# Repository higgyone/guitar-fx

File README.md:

# guitar-fx
Creating guitar pedal effects using an FPGA and VHDL. This is a learning experience to understand how to write digital signal processing effects for an FPGA

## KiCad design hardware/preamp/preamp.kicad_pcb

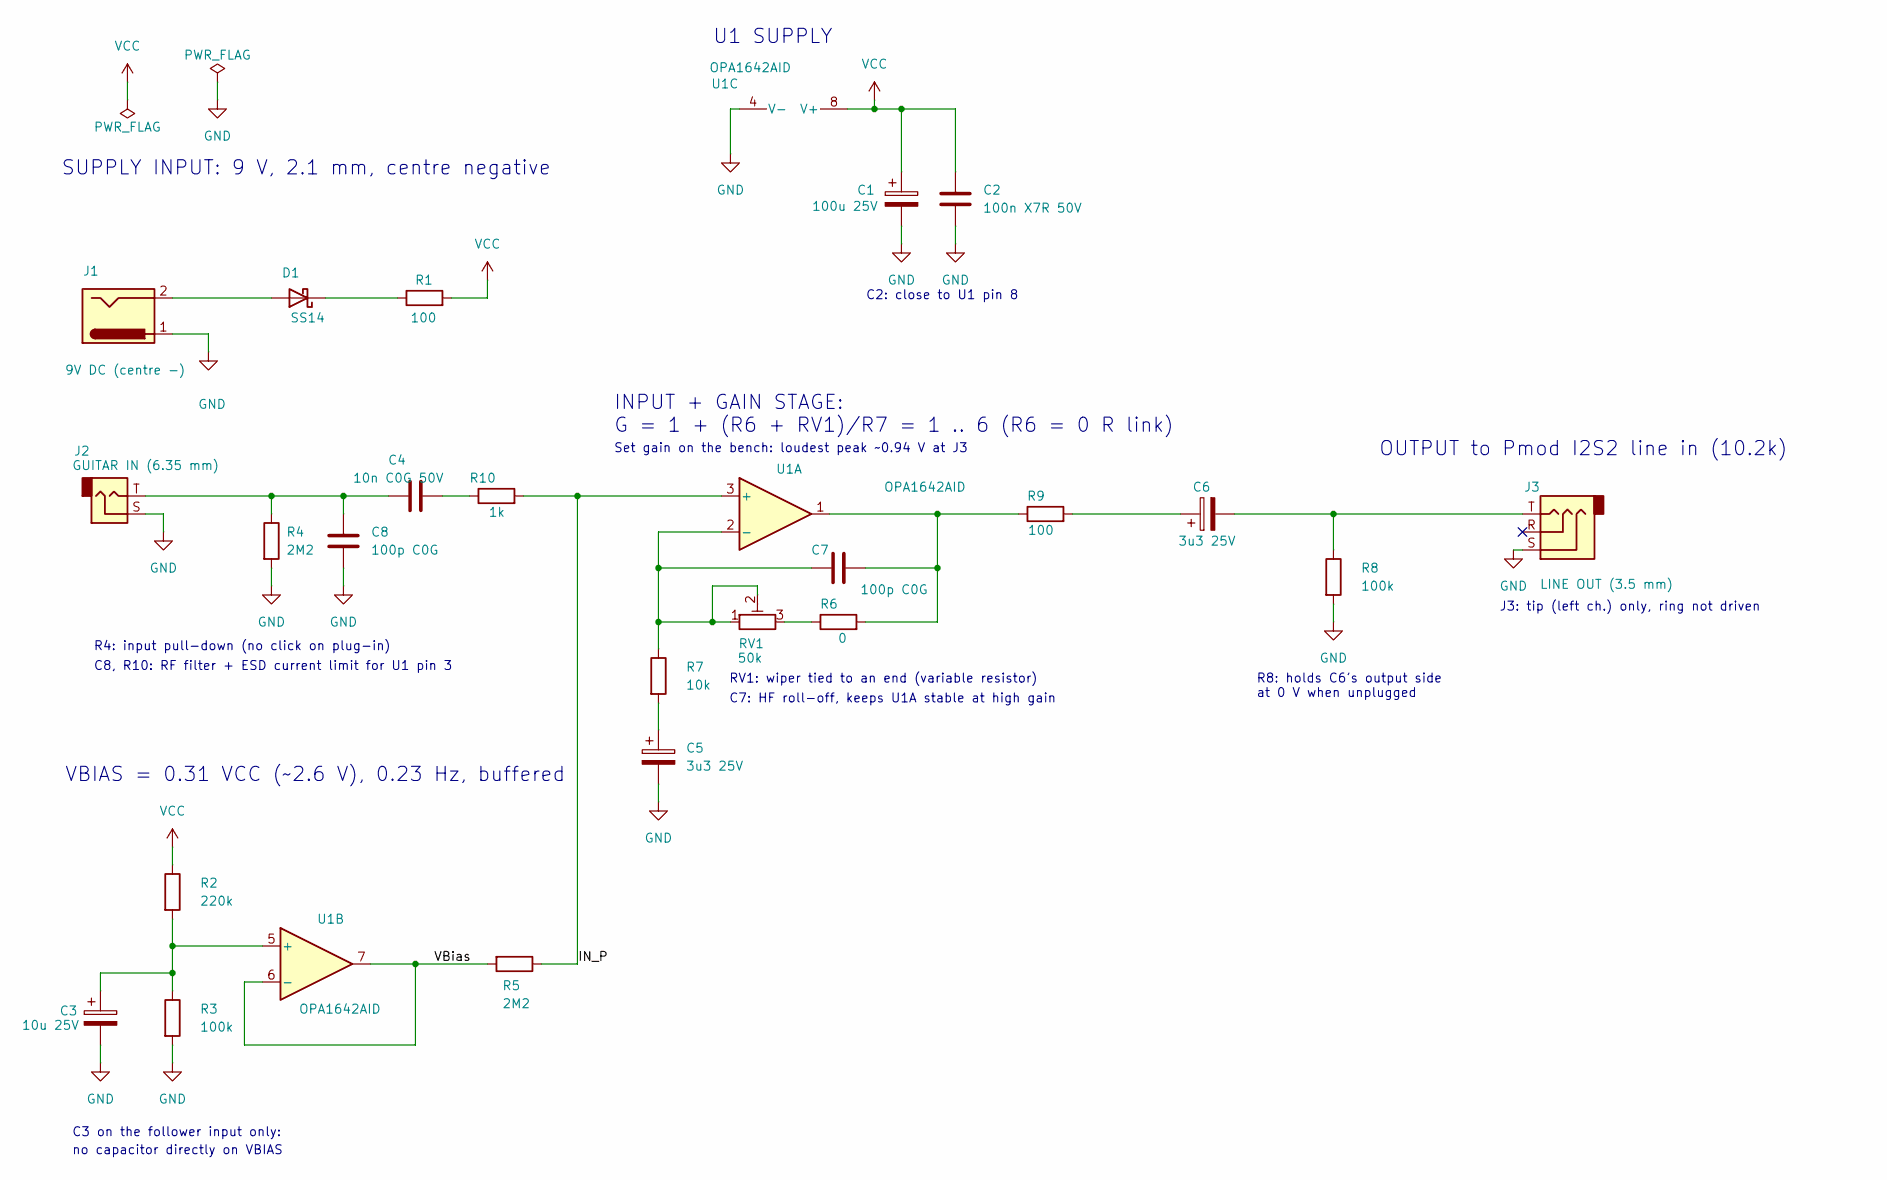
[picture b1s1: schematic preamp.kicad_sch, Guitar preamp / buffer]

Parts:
C1: 100u 25V; CP_Elec_6.3x7.7
C2: 100n X7R 50V; C_0603_1608Metric_Pad1.08x0.95mm_HandSolder
C3: 10u 25V; CP_Elec_4x5.4
C4: 10n C0G 50V; C_0402_1005Metric_Pad0.74x0.62mm_HandSolder
C5, C6: 3u3 25V; CP_Elec_4x5.4
C7: 100p C0G; C_0402_1005Metric_Pad0.74x0.62mm_HandSolder
C8: 100p C0G; C_0603_1608Metric_Pad1.08x0.95mm_HandSolder
D1: SS14; D_SMA_Handsoldering
J1: 9V DC (centre -); BarrelJack_CUI_PJ-102AH_Horizontal
J2: GUITAR IN (6.35 mm); Jack_6.35mm_Neutrik_NMJ4HCD2_Horizontal
J3: LINE OUT (3.5 mm); Jack_3.5mm_CUI_SJ1-3523N_Horizontal
R1, R9: 100; R_0603_1608Metric_Pad0.98x0.95mm_HandSolder
R2: 220k; R_0603_1608Metric_Pad0.98x0.95mm_HandSolder
R3, R8: 100k; R_0603_1608Metric_Pad0.98x0.95mm_HandSolder
R4, R5: 2M2; R_0603_1608Metric_Pad0.98x0.95mm_HandSolder
R6: 0; R_0603_1608Metric_Pad0.98x0.95mm_HandSolder
R7: 10k; R_0603_1608Metric_Pad0.98x0.95mm_HandSolder
R10: 1k; R_0603_1608Metric_Pad0.98x0.95mm_HandSolder
RV1: 50k; Potentiometer_Bourns_3296W_Vertical
U1: OPA1642AID; SOIC-8_3.9x4.9mm_P1.27mm

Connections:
/IN_P: R5.1, R10.2, U1.3 (+)
/VBias: R5.2, U1.6 (-), U1.7
GND: C1.2, C2.2, C3.2, C5.2, C8.2, J1.1, J2.S, J3.S, R3.2, R4.2, R8.2, U1.4 (V-)
unnamed: C4.1, C8.1, J2.T, R4.1
unnamed: C4.2, R10.1
unnamed: C5.1, R7.2
unnamed: C6.1, R9.2
unnamed: C6.2, J3.T, R8.1
unnamed: C7.2, R6.2, R9.1, U1.1
unnamed: D1.2 (A), J1.2
unnamed: D1.1 (K), R1.1
unnamed: R6.1, RV1.3
unnamed: C7.1, R7.1, RV1.1, RV1.2, U1.2 (-)
unnamed: C3.1, R2.2, R3.1, U1.5 (+)
VCC: C1.1, C2.1, R1.2, R2.1, U1.8 (V+)

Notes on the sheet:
C3 on the follower input only:
R8: holds C6's output side at 0 V when unplugged
SUPPLY INPUT: 9 V, 2.1 mm, centre negative
no capacitor directly on VBIAS
J3: tip (left ch.) only, ring not driven
Set gain on the bench: loudest peak ~0.94 V at J3
INPUT + GAIN STAGE: G = 1 + (R6 + RV1)/R7 = 1 .. 6 (R6 = 0 R link)
R4: input pull-down (no click on plug-in)
C2: close to U1 pin 8
RV1: wiper tied to an end (variable resistor)
OUTPUT to Pmod I2S2 line in (10.2k)
VBIAS = 0.31 VCC (~2.6 V), 0.23 Hz, buffered
U1 SUPPLY
C8, R10: RF filter + ESD current limit for U1 pin 3
C7: HF roll-off, keeps U1A stable at high gain

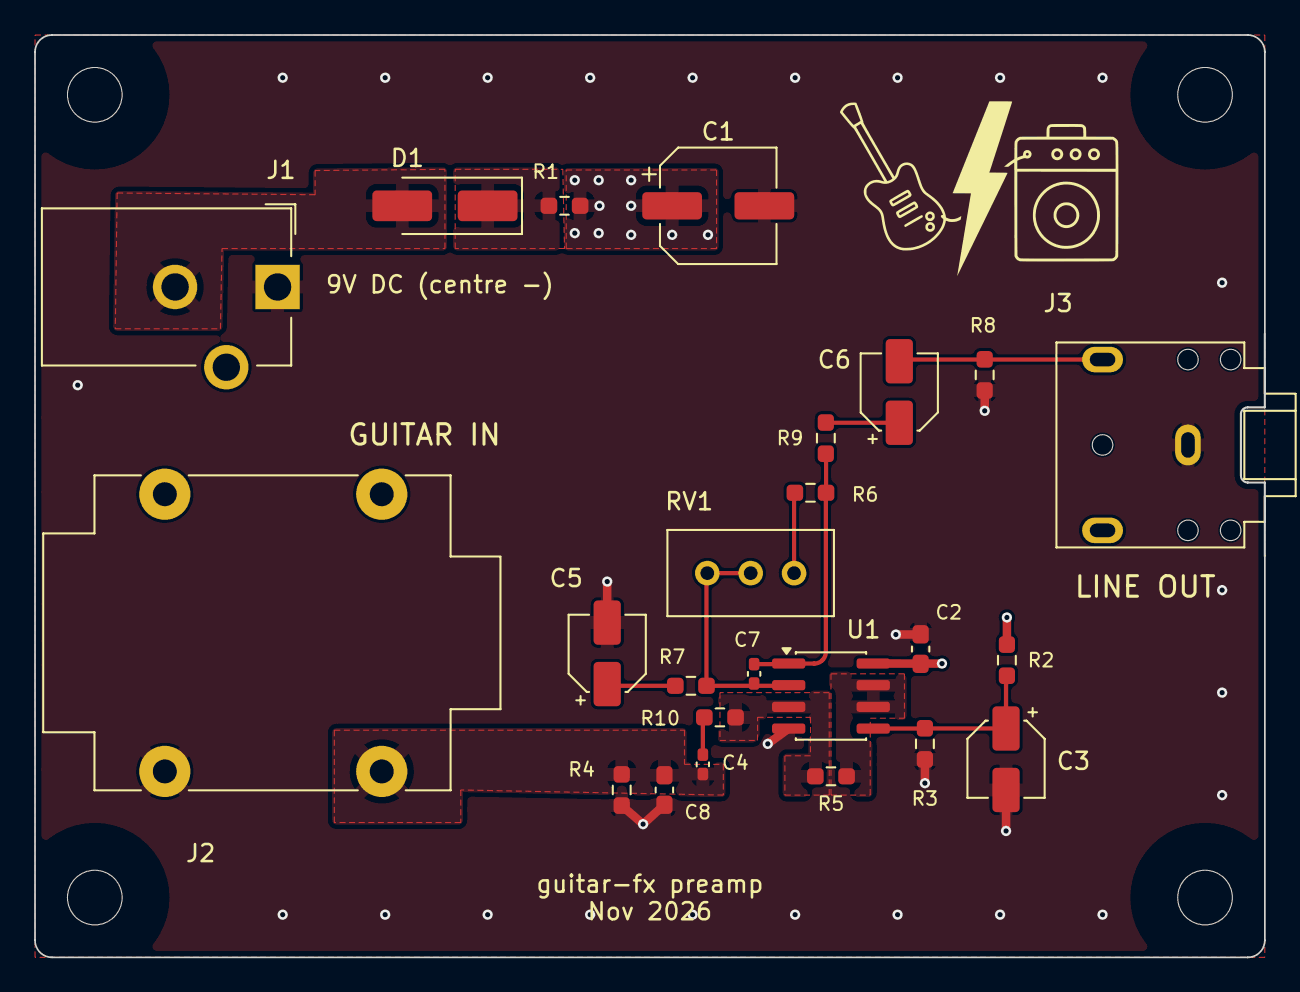
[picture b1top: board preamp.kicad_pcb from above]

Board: 4 copper layers, 72.0 x 54.0 mm, 28 parts (0 on the bottom side), 15 nets.

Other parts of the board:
H1, H2, H3, H4: M3; MountingHole_3.2mm_M3

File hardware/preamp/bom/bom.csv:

Ref,Qty per board,Value,Footprint,Manufacturer,MPN,Notes
U1,1,OPA1642AID,SOIC-8,Texas Instruments,OPA1642AID,DigiKey only (not at Mouser or RS)
J1,1,DC jack 2.0 mm pin (centre -),BarrelJack_CUI_PJ-102AH_Horizontal,Same Sky,PJ-102AH,
J2,1,6.35 mm mono switched,Jack_6.35mm_Neutrik_NMJ4HCD2_Horizontal,Neutrik,NMJ4HCD2,
J3,1,3.5 mm stereo,Jack_3.5mm_CUI_SJ1-3523N_Horizontal,Same Sky,SJ1-3523N,
D1,1,SS14 40 V 1 A Schottky,D_SMA,Vishay,SS14-E3/61T,Any SMA SS14 (onsemi SS14 at RS)
RV1,1,50k multi-turn trimmer,Bourns 3296W,Bourns,3296W-1-503LF,
C1,1,100u 25V,CP_Elec_6.3x7.7,Nichicon,UCD1E101MCL1GS,Or Panasonic EEE-FK1E101P (RS has it; Mouser/DigiKey out of stock)
C2,1,100n X7R 50V,0603,Yageo,CC0603KRX7R9BB104,
C3,1,10u 25V,CP_Elec_4x5.4,Panasonic,EEE-FK1E100R,
C4,1,10n C0G 50V,0402,Murata,GRM1555C1H103JE01D,
C5 C6,2,3u3 25V,CP_Elec_4x5.4,Panasonic,EEE-1EA3R3NR,4 x 5.4 mm S series
C7,1,100p C0G 50V,0402,Murata,GRM1555C1H101JA01D,
C8,1,100p C0G 50V,0603,Murata,GRM1885C1H101JA01D,
R1 R9,2,100R 1%,0603,Yageo,RC0603FR-07100RL,
R10,1,1k 1%,0603,Yageo,RC0603FR-071KL,
R7,1,10k 1%,0603,Yageo,RC0603FR-0710KL,
R3 R8,2,100k 1%,0603,Yageo,RC0603FR-07100KL,
R2,1,220k 1%,0603,Yageo,RC0603FR-07220KL,
R4 R5,2,2M2 1%,0603,Yageo,RC0603FR-072M2L,
R6,1,0R link,0603,Yageo,RC0603JR-070RL,
-,1,Pmod I2S2,-,Digilent,410-379,Not on the PCB: ADC/DAC module for the Arty
